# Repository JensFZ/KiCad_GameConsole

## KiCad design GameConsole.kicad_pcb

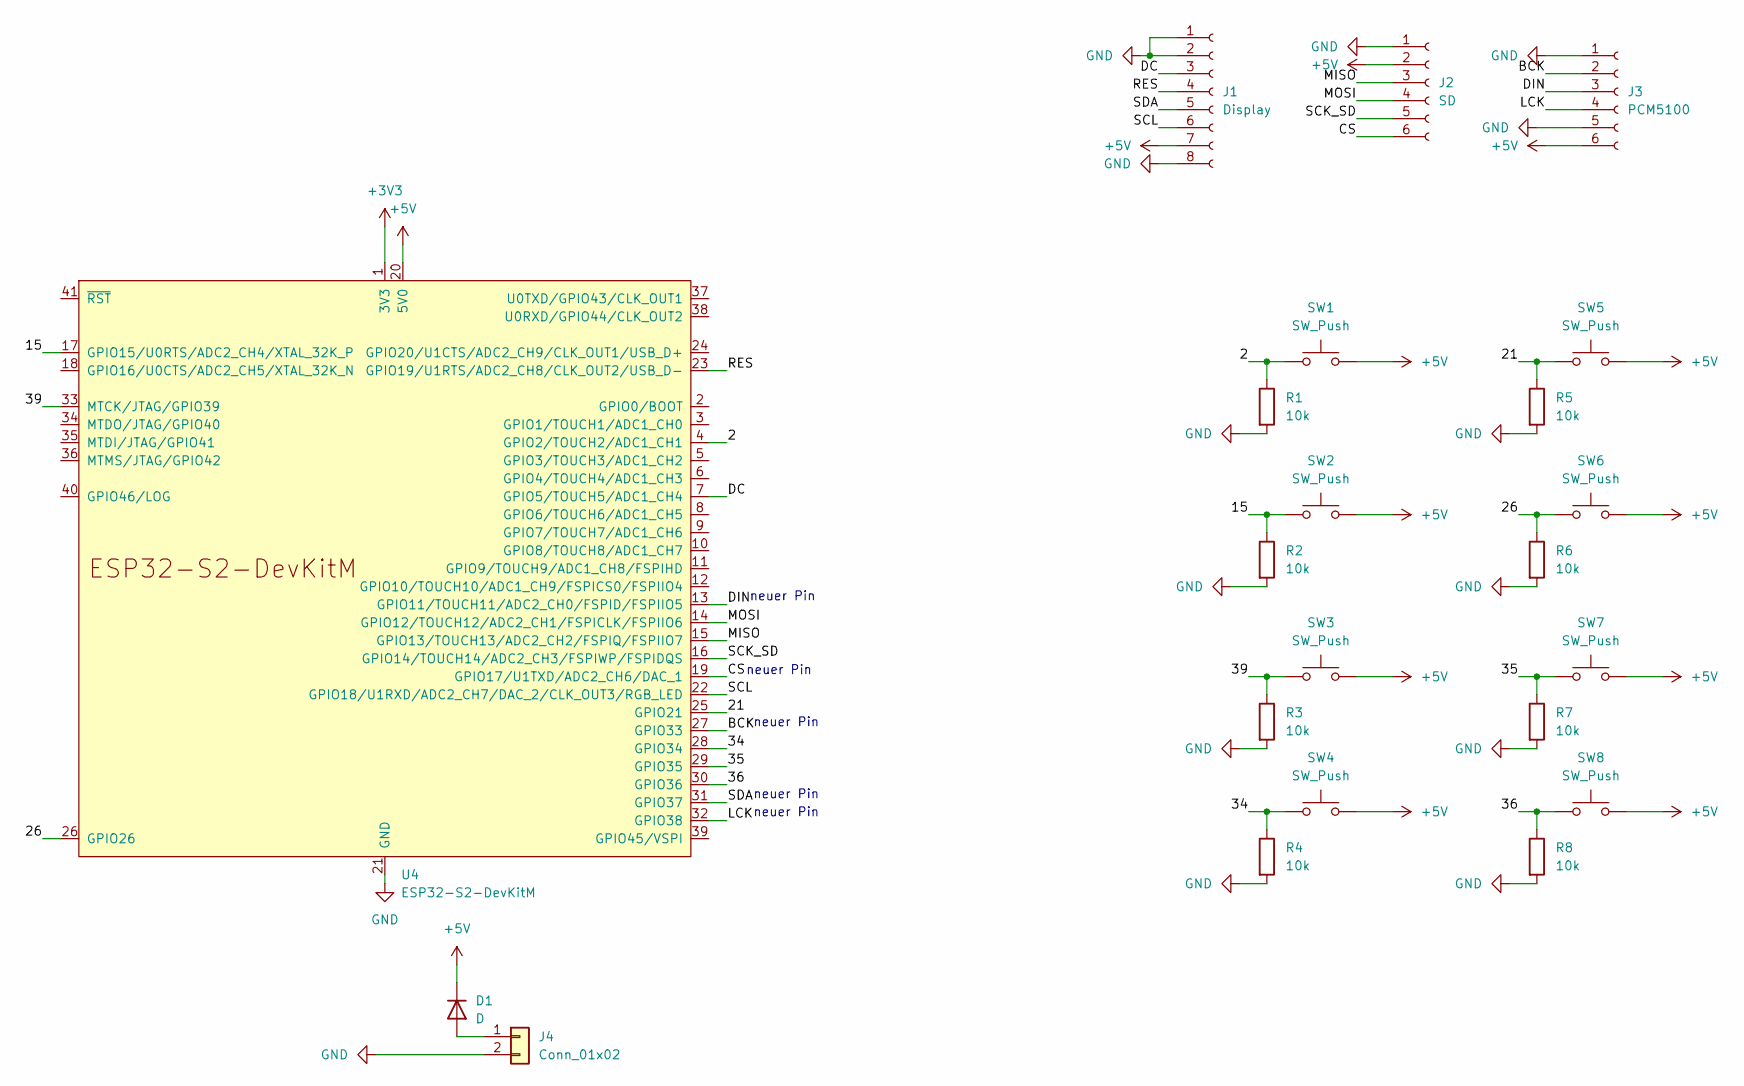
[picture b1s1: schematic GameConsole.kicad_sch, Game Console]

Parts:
D1: D; D_A-405_P10.16mm_Horizontal
J1: Display; PinSocket_1x08_P2.54mm_Vertical
J2: SD; PinSocket_1x06_P2.54mm_Vertical
J3: PCM5100; PinSocket_1x06_P2.54mm_Vertical
J4: Conn_01x02; SolderWire-0.127sqmm_1x02_P3.7mm_D0.48mm_OD1mm
R1, R2, R3, R4, R5, R6, R7, R8: 10k; R_Axial_DIN0207_L6.3mm_D2.5mm_P10.16mm_Horizontal
SW1, SW2, SW3, SW4, SW5, SW6, SW7, SW8: SW_Push; SW_PUSH_6mm_H4.3mm
U4: ESP32-S2-DevKitM

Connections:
+3V3: U4.1 (3V3)
+5V: D1.1 (K), J1.7, J2.2, J3.6, SW1.2, SW2.2, SW3.2, SW4.2, SW5.2, SW6.2, SW7.2, SW8.2, U4.20 (5V0)
/2: R1.1, SW1.1, U4.4 (GPIO2/TOUCH2/ADC1_CH1)
/15: R2.1, SW2.1, U4.17 (GPIO15/U0RTS/ADC2_CH4/XTAL_32K_P)
/21: R5.1, SW5.1, U4.25 (GPIO21)
/26: R6.1, SW6.1, U4.26 (GPIO26)
/34: R4.1, SW4.1, U4.28 (GPIO34)
/35: R7.1, SW7.1, U4.29 (GPIO35)
/36: R8.1, SW8.1, U4.30 (GPIO36)
/39: R3.1, SW3.1, U4.33 (MTCK/JTAG/GPIO39)
/BCK: J3.2, U4.27 (GPIO33)
/CS: J2.6, U4.19 (GPIO17/U1TXD/ADC2_CH6/DAC_1)
/DC: J1.3, U4.7 (GPIO5/TOUCH5/ADC1_CH4)
/DIN: J3.3, U4.13 (GPIO11/TOUCH11/ADC2_CH0/FSPID/FSPIIO5)
/LCK: J3.4, U4.32 (GPIO38)
/MISO: J2.3, U4.15 (GPIO13/TOUCH13/ADC2_CH2/FSPIQ/FSPIIO7)
/MOSI: J2.4, U4.14 (GPIO12/TOUCH12/ADC2_CH1/FSPICLK/FSPIIO6)
/RES: J1.4, U4.23 (GPIO19/U1RTS/ADC2_CH8/CLK_OUT2/USB_D-)
/SCK_SD: J2.5, U4.16 (GPIO14/TOUCH14/ADC2_CH3/FSPIWP/FSPIDQS)
/SCL: J1.6, U4.22 (GPIO18/U1RXD/ADC2_CH7/DAC_2/CLK_OUT3/RG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)
/SDA: J1.5, U4.31 (GPIO37)
GND: J1.1, J1.2, J1.8, J2.1, J3.1, J3.5, J4.2, R1.2, R2.2, R3.2, R4.2, R5.2, R6.2, R7.2, R8.2, U4.21 (GND), U4.42 (GND)
unnamed: D1.2 (A), J4.1

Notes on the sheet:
neuer Pin

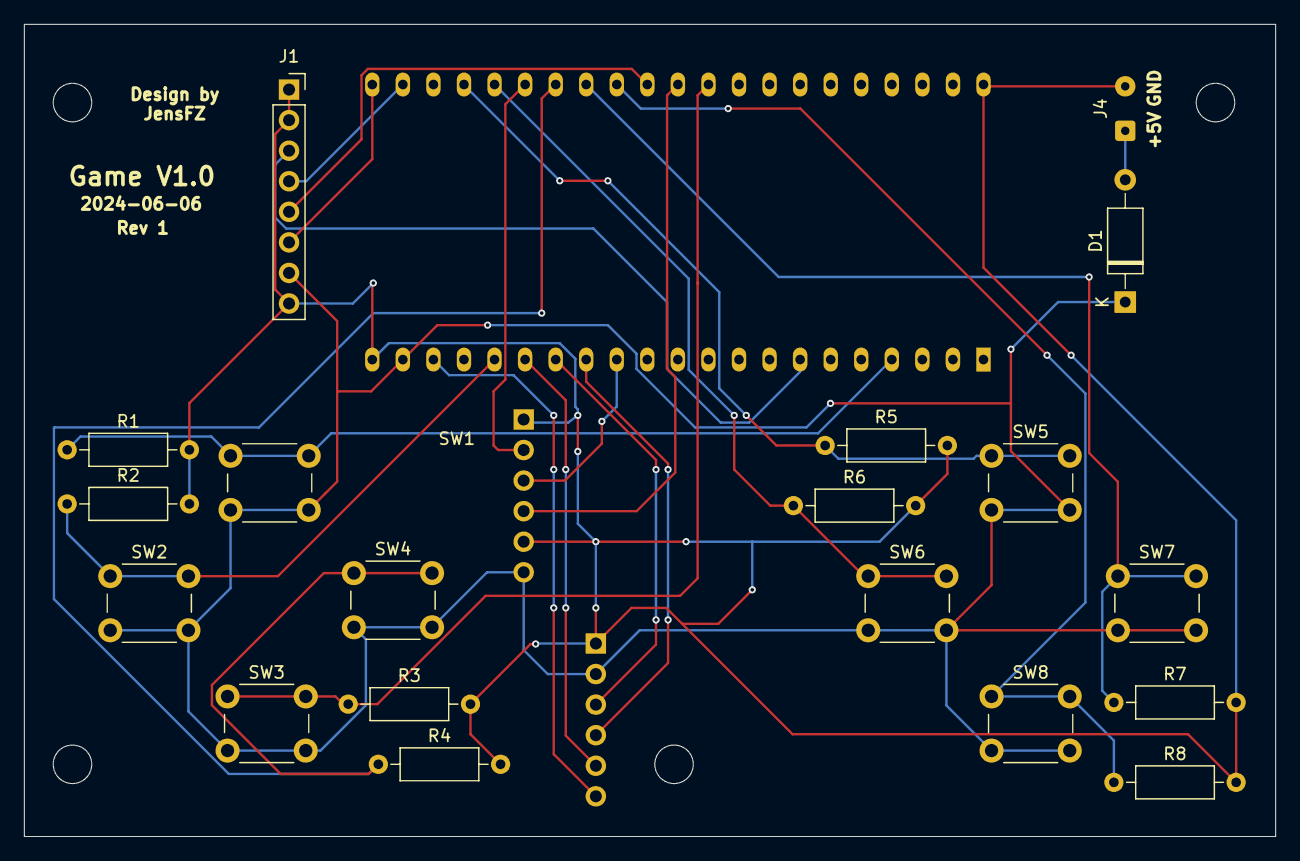
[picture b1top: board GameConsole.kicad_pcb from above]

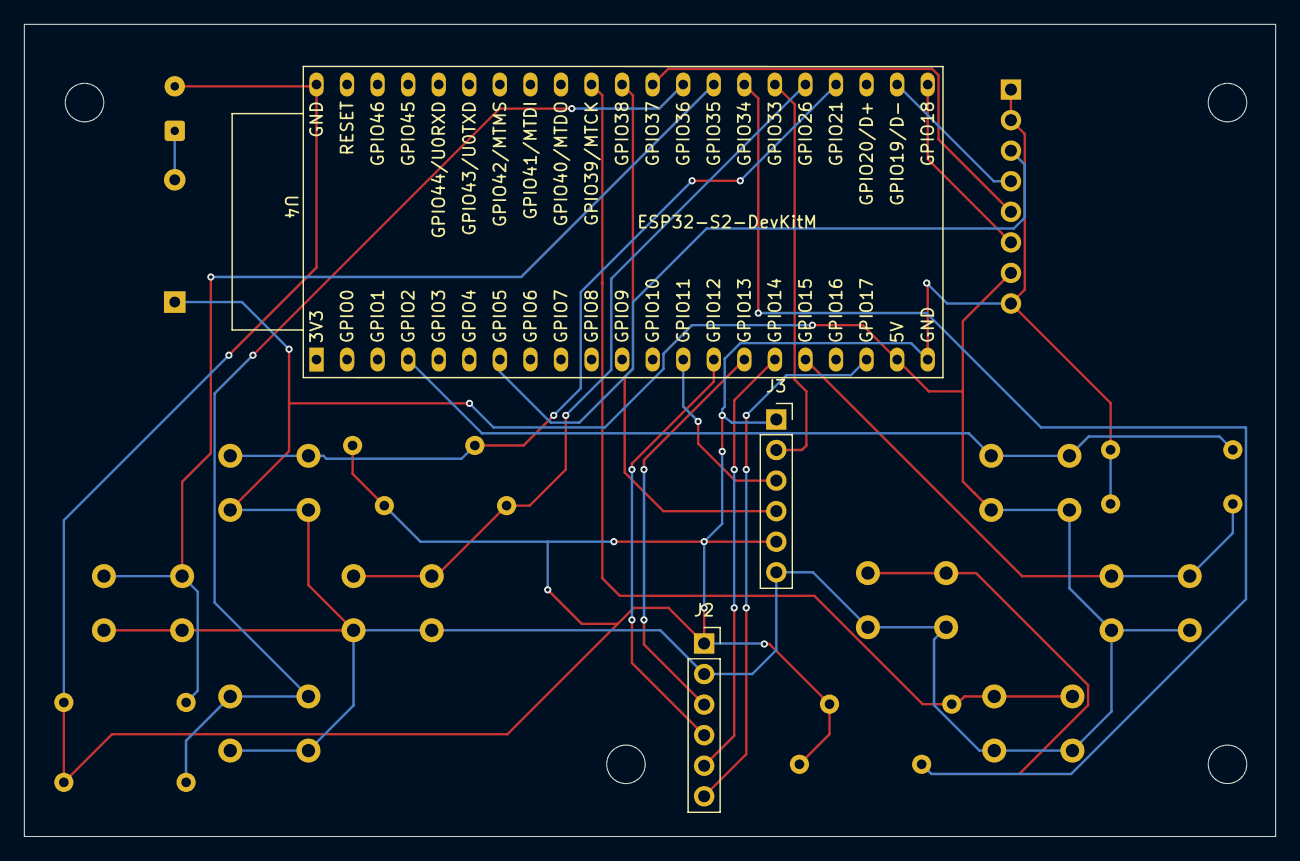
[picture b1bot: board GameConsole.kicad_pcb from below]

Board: 2 copper layers, 104.0 x 67.5 mm, 22 parts (3 on the bottom side), 22 nets.

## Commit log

2024-06-07 Pinheader durch Socket ersetzt
